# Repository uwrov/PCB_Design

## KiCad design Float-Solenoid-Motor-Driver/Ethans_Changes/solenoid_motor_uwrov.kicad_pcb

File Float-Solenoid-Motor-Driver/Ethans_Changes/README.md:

# uw-rov-solenoid-motor

Tracd widths are quite sketch and the whole layout is a little sus but overall this should be the same design as we have on the protoboard.

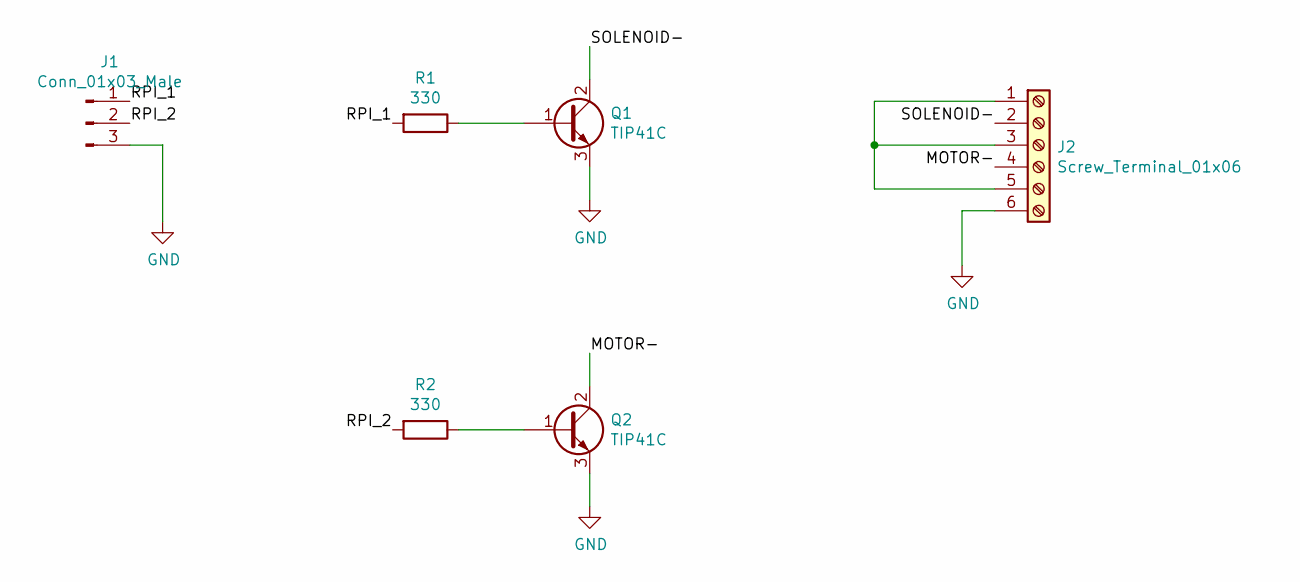
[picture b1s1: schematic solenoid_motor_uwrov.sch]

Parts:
J1: Conn_01x03_Male; PinHeader_1x03_P2.54mm_Vertical
J2: Screw_Terminal_01x06; TerminalBlock_MetzConnect_Type011_RT05506HBWC_1x06_P5.00mm_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
Q1, Q2: TIP41C; TO-220-3_Vertical
R1, R2: 330; R_Axial_DIN0207_L6.3mm_D2.5mm_P2.54mm_Vertical

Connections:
/MOTOR-: J2.4, Q2.2 (C)
/RPI_1: J1.1, R1.2
/RPI_2: J1.2, R2.2
/SOLENOID-: J2.2, Q1.2 (C)
GND: J1.3, J2.6, Q1.3 (E), Q2.3 (E)
unnamed: J2.1, J2.3, J2.5
unnamed: Q1.1 (B), R1.1
unnamed: Q2.1 (B), R2.1

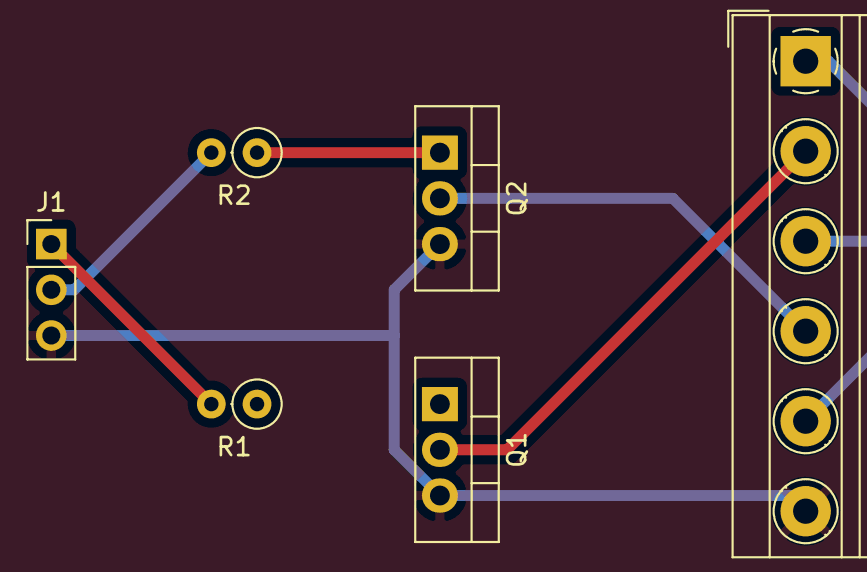
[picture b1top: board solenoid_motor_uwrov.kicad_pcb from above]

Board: 2 copper layers, 6 parts (0 on the bottom side), 8 nets.

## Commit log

2021-11-06 dummy_test
2021-11-06 git ignore
